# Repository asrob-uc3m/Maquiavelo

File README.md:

Maquiavelo> line follower robot

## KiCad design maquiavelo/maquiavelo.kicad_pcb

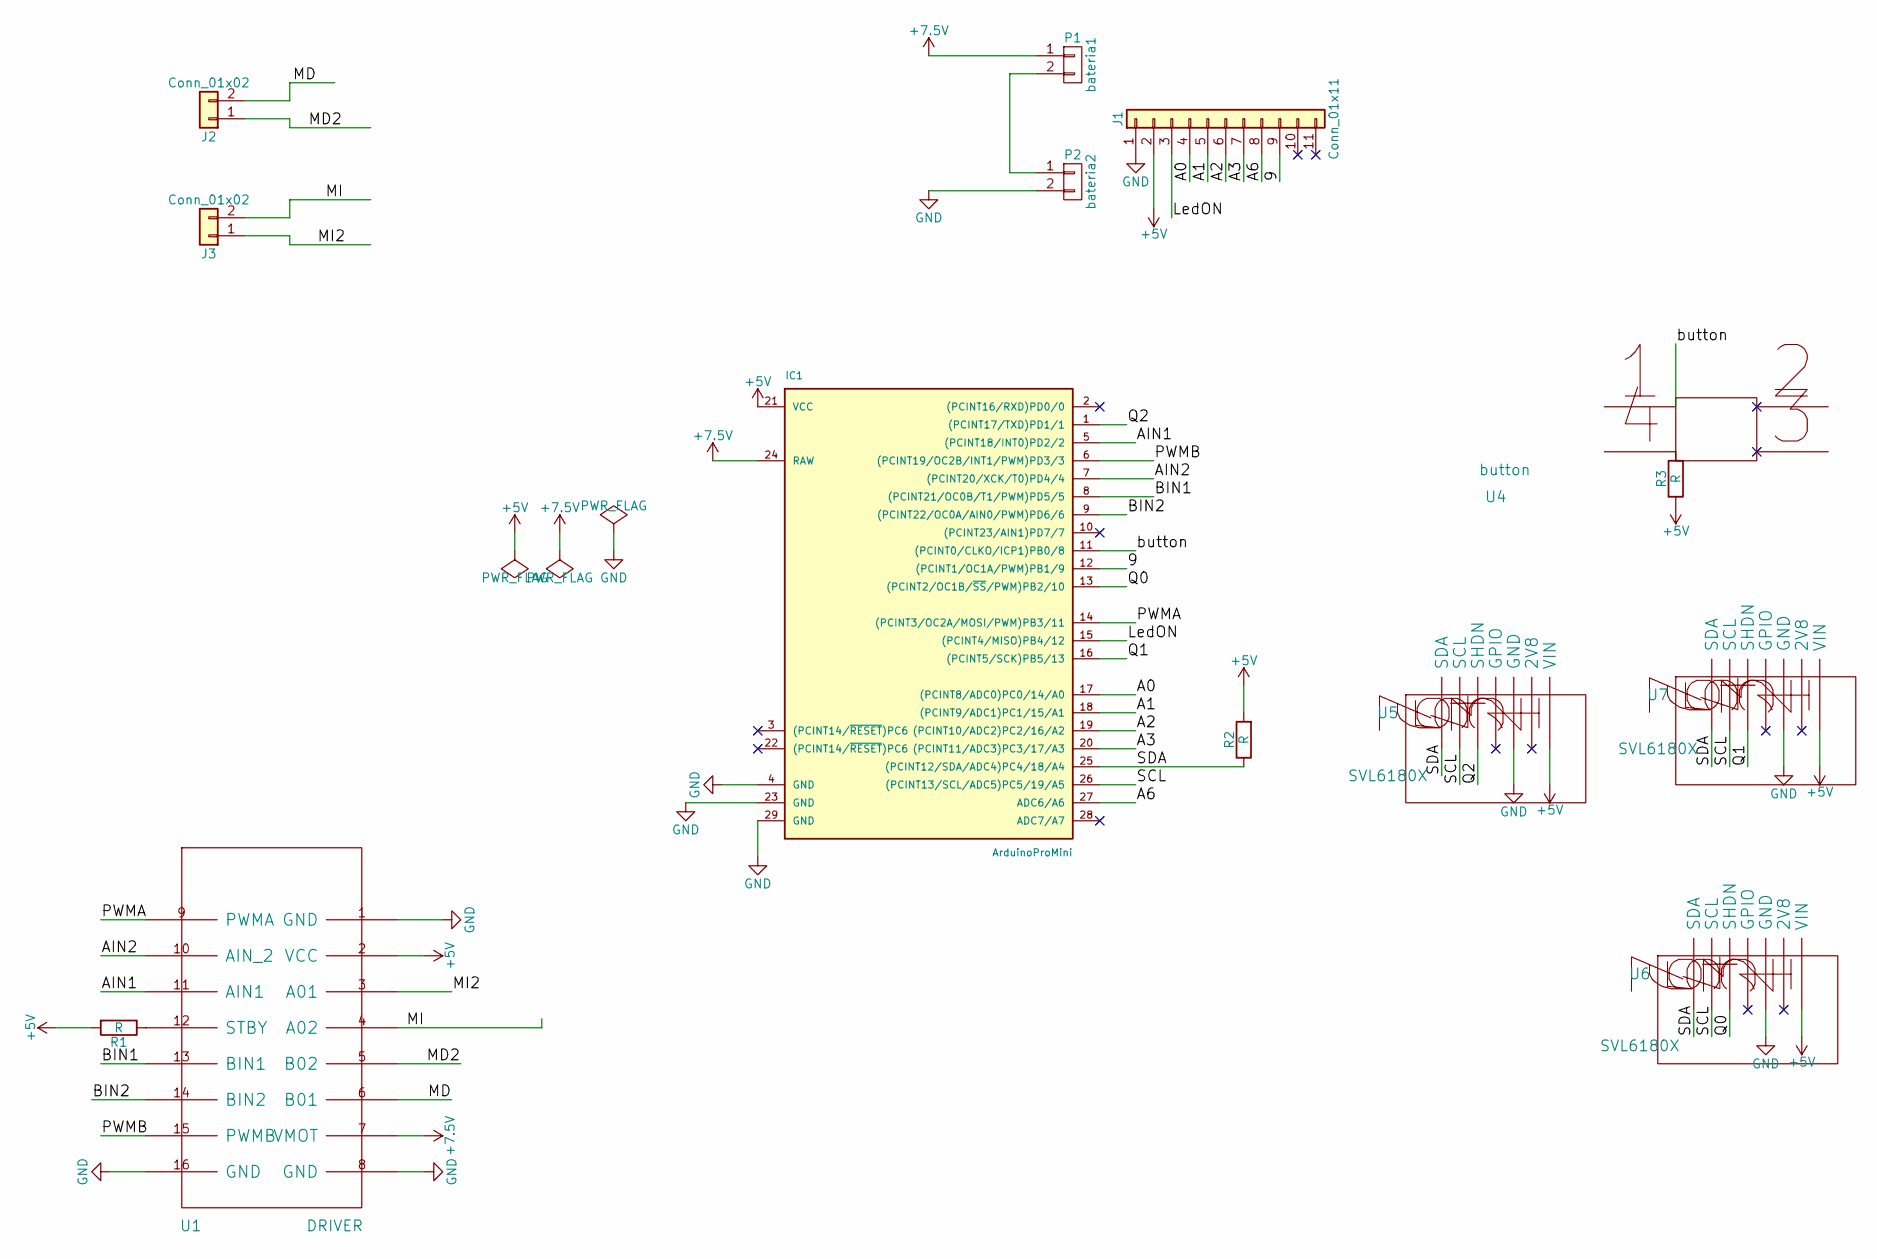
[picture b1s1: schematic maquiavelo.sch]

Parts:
IC1: ArduinoProMini; pro_mini
J1: Conn_01x11; Pin_Header_Straight_1x11_Pitch2.54mm
J2, J3: Conn_01x02; Pin_Header_Straight_1x02_Pitch2.54mm
P1: bateria1; JST_XH_B02B-XH-A_02x2.50mm_Straight
P2: bateria2; JST_XH_B02B-XH-A_02x2.50mm_Straight
R1, R2, R3: R; R_Axial_DIN0207_L6.3mm_D2.5mm_P7.62mm_Horizontal
U1: DRIVER; driver
U4: button; SW_MEC_5GTH9
U5, U6, U7: SVL6180X; Pin_Header_Straight_1x07_Pitch2.54mm

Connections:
+5V: IC1.21 (VCC), J1.2, R1.2, R2.2, R3.1, U1.2 (VCC), U5.1 (VIN), U6.1 (VIN), U7.1 (VIN)
+7.5V: IC1.24 (RAW), P1.1, U1.7 (VMOT)
/9: IC1.12 ((PCINT1/OC1A/PWM)PB1/9), J1.9
/A0: IC1.17 ((PCINT8/ADC0)PC0/14/A0), J1.4
/A1: IC1.18 ((PCINT9/ADC1)PC1/15/A1), J1.5
/A2: IC1.19 ((PCINT10/ADC2)PC2/16/A2), J1.6
/A3: IC1.20 ((PCINT11/ADC3)PC3/17/A3), J1.7
/A6: IC1.27 (ADC6/A6), J1.8
/AIN1: IC1.5 ((PCINT18/INT0)PD2/2), U1.11 (AIN1)
/AIN2: IC1.7 ((PCINT20/XCK/T0)PD4/4), U1.10 (AIN_2)
/BIN1: IC1.8 ((PCINT21/OC0B/T1/PWM)PD5/5), U1.13 (BIN1)
/BIN2: IC1.9 ((PCINT22/OC0A/AIN0/PWM)PD6/6), U1.14 (BIN2)
/LedON: IC1.15 ((PCINT4/MISO)PB4/12), J1.3
/MD: J2.2, U1.6 (B01)
/MD2: J2.1, U1.5 (B02)
/MI: J3.2, U1.4 (A02)
/MI2: J3.1, U1.3 (A01)
/PWMA: IC1.14 ((PCINT3/OC2A/MOSI/PWM)PB3/11), U1.9 (PWMA)
/PWMB: IC1.6 ((PCINT19/OC2B/INT1/PWM)PD3/3), U1.15 (PWMB)
/Q0: IC1.13 ((PCINT2/OC1B/~SS~/PWM)PB2/10), U6.5 (SHDN)
/Q1: IC1.16 ((PCINT5/SCK)PB5/13), U7.5 (SHDN)
/Q2: IC1.1 ((PCINT17/TXD)PD1/1), U5.5 (SHDN)
/SCL: IC1.26 ((PCINT13/SCL/ADC5)PC5/19/A5), U5.6 (SCL), U6.6 (SCL), U7.6 (SCL)
/SDA: IC1.25 ((PCINT12/SDA/ADC4)PC4/18/A4), R2.1, U5.7 (SDA), U6.7 (SDA), U7.7 (SDA)
/button: IC1.11 ((PCINT0/CLKO/ICP1)PB0/8), U4.1
GND: IC1.4 (GND), IC1.23 (GND), IC1.29 (GND), J1.1, P2.2, U1.1 (GND), U1.8 (GND), U1.16 (GND), U5.3 (GND), U6.3 (GND), U7.3 (GND)
unnamed: P1.2, P2.1
unnamed: R1.1, U1.12 (STBY)
unnamed: R3.2, U4.4

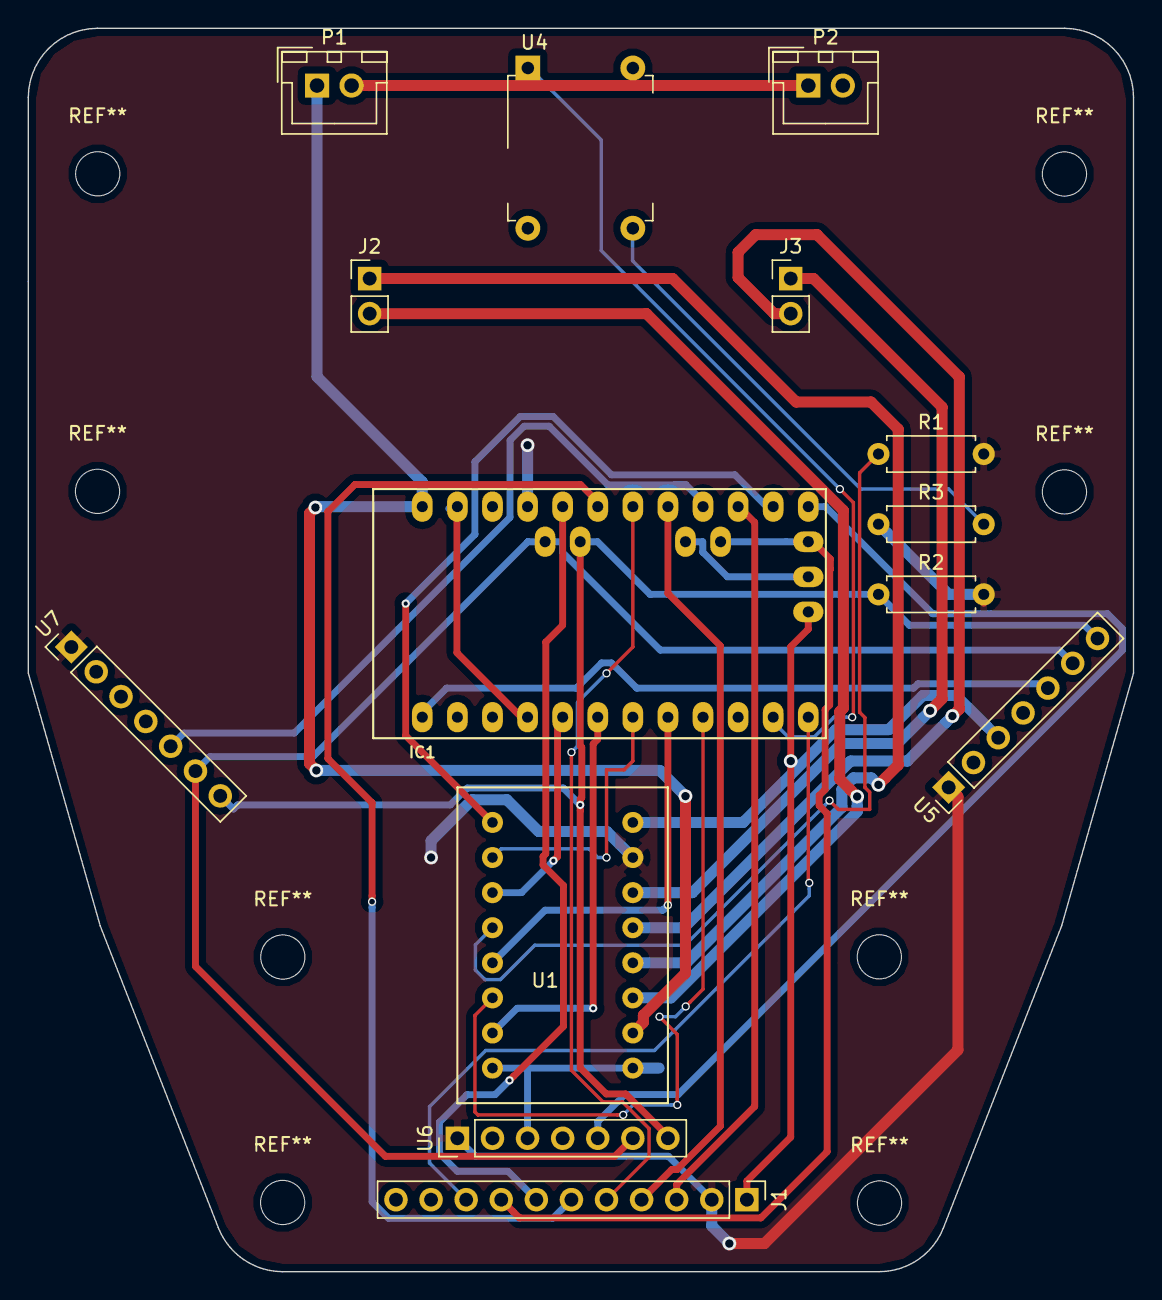
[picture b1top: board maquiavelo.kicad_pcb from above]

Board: 2 copper layers, 80.0 x 90.0 mm, 14 parts (0 on the bottom side), 29 nets.

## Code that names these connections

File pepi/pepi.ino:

//VELOCISTA DEFINITIVO 
#include <QTRSensors.h>

//DECLARACION DE ENTRADAS///////////////
//BOTONES

const int btn1 = 8;

int cruzero = 120 ;//VELOCIDAD DE CURCERO ;D   

int pwma = 3;
int ain2 = 4;
int ain1 = 2;
int pwmb = 11;
int bin2 = 7;
int bin1 = 6;

int P = 0; 
int I = 0;
int D = 0;
int LAST = 0;
float vel;

#define NUM_SENSORS   6     // NUMERO DE SENSORES USADOS
#define TIMEOUT       2500     // TIEMPO DE ESPERA QUE PONE SALIDAS EN LOW
#define EMITTER_PIN   12    

//EL 12 ES EL 12, EL 14 = A0 Y SUSECIVAMENTE  
QTRSensorsRC qtrrc((unsigned char[]) {19, 18, 17, 16, 15, 14, 11, 12},
  NUM_SENSORS, TIMEOUT, EMITTER_PIN); 
unsigned int sensorValues[NUM_SENSORS];

unsigned int position = 0;

void setup()
{

  pinMode(btn1, INPUT);
    
  pinMode(pwma,OUTPUT);
  pinMode(ain1,OUTPUT);
  pinMode(ain2,OUTPUT);
  pinMode(pwmb,OUTPUT);
  pinMode(bin1,OUTPUT);
  pinMode(bin2,OUTPUT);
  
  pinMode(13,OUTPUT);

  //Serial.begin(9600);
  delay(1500);
  digitalWrite(13, HIGH);
   for (int j = 0; j < 40; j++)  
 {                                 
                    
  qtrrc.calibrate();     //FUNCIÓN QUE CALIBRA EL SENSOR

 }
 
 digitalWrite(13, LOW); 
                                                                   
 digitalWrite(ain1,LOW);
 digitalWrite(ain2,HIGH);
 
 digitalWrite(bin1,HIGH);
 digitalWrite(bin2,LOW);
 
 analogWrite(pwma,0);
 analogWrite(pwmb,0);
}


void loop()
{
  //Serial.println(ain1);
  if (digitalRead(btn1) == 1){
    for(;;){ 
  
      qtrrc.read(sensorValues);
      position = qtrrc.readLine(sensorValues, QTR_EMITTERS_ON, 0);
      // Serial.println(position);                                                                                                  
      P = ((position)-(2500)); /// ERROR ACUMULADO
  /////FRENOS////
      if(P < -2500){
        analogWrite(pwma,150); // VELOCIDAD PARA EL MOTOR DERECHO 
        analogWrite(pwmb,90); //  VELOCIDAD PARA EL MOTOR IZQUIERDO
        digitalWrite(ain1,LOW);   ///FRENTE
        digitalWrite(ain2,HIGH);
        digitalWrite(bin1,LOW);  ///RETROCEDE
        digitalWrite(bin2,HIGH);  
      } else if (P > 2500){
        analogWrite(pwma,150); // VELOCIDAD PARA EL MOTOR DERECHO
        analogWrite(pwmb,90); //  VELOCIDAD PARA EL MOTOR IZQUIERDO
        digitalWrite(ain1,HIGH);   ///RETROCEDE
        digitalWrite(ain2,LOW);
        digitalWrite(bin1,HIGH);  ///FRENTE
        digitalWrite(bin2,LOW);

      }
        /////////////////////////
      else{
        D = (P - LAST); /// ERROR MENOS EL ERROR ANTERIOR , DERIVATIVO
        I = (P + LAST); //INTEGRAL
        vel = (P*0.18) + (D*4 ) + (I*0.001 );// para velocidad 120//////estaba en 0.0925
        if(vel > cruzero) vel = cruzero;
        if(vel < -cruzero) vel = -cruzero;

        analogWrite(pwma,cruzero - vel); // VELOCIDAD PARA EL MOTOR DERECHO
        analogWrite(pwmb,cruzero + vel); //  VELOCIDAD PARA EL MOTOR IZQUIERDO

        digitalWrite(ain1,LOW);   ///FRENTE
        digitalWrite(ain2,HIGH);
        digitalWrite(bin1,HIGH);  ///FRENTE
        digitalWrite(bin2,LOW);
        LAST = P; //ERROR ANTERIOR 
        }
}////BUCLE INFINITO
}///PRESIONO BOTON
}///FIN DEL LOOP

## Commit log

2017-12-19 Commit inicial
2017-12-19 primera version codigo SIN PID
2017-12-27 pid
    codigo con PID
2017-12-27 codigo sin PID
2018-02-15 pcb
    falta acabar la pcb
2018-03-17 Configuracion modulo bluetooth
    Con esto al cambiar el codigo en upload ya se sube directamente al arduino
2018-03-27 PID COMPLETO
    PID completo a falta de control manual con arduino.
2018-03-30 FRITZING CUTRE MAQUIAVELO
    Pues eso, pongo el fichetro fritzing para cuando estoy con Dª Mar y no perder el tiempo en volverlo a hacer.
    PD: <3 Mar
2018-06-21 Rename sketch_dec13a.ino to Codigo_Sin_PID.ino
2018-06-25 PCB empaquetada
    Faltan las pistas de cobre, poner los taladros como componentes y exportar los archivos en el formato adecuado
2018-07-07 Archivos gerber + archivo de taladros para pcb
2018-09-09 PCB files (W/out Gerber files)
2018-09-12 file redistribution :unicorn:
2018-09-13 gerbers
2018-11-05 fix pin config
2018-11-09 fixed sensor order and PID rate
2018-11-21 alargador motores
2019-02-27 Carpeta de Maquiavelo
2019-02-27 codigo de Maquiavelo (1) y configuracion modulo BT
2019-02-27 Gerber files
2019-02-27 Motor 3D files
2019-02-27 Schematic and PCB files
2019-02-27 libraries needed for PCB files
2019-03-06 assembly model
2019-08-17 reordering
